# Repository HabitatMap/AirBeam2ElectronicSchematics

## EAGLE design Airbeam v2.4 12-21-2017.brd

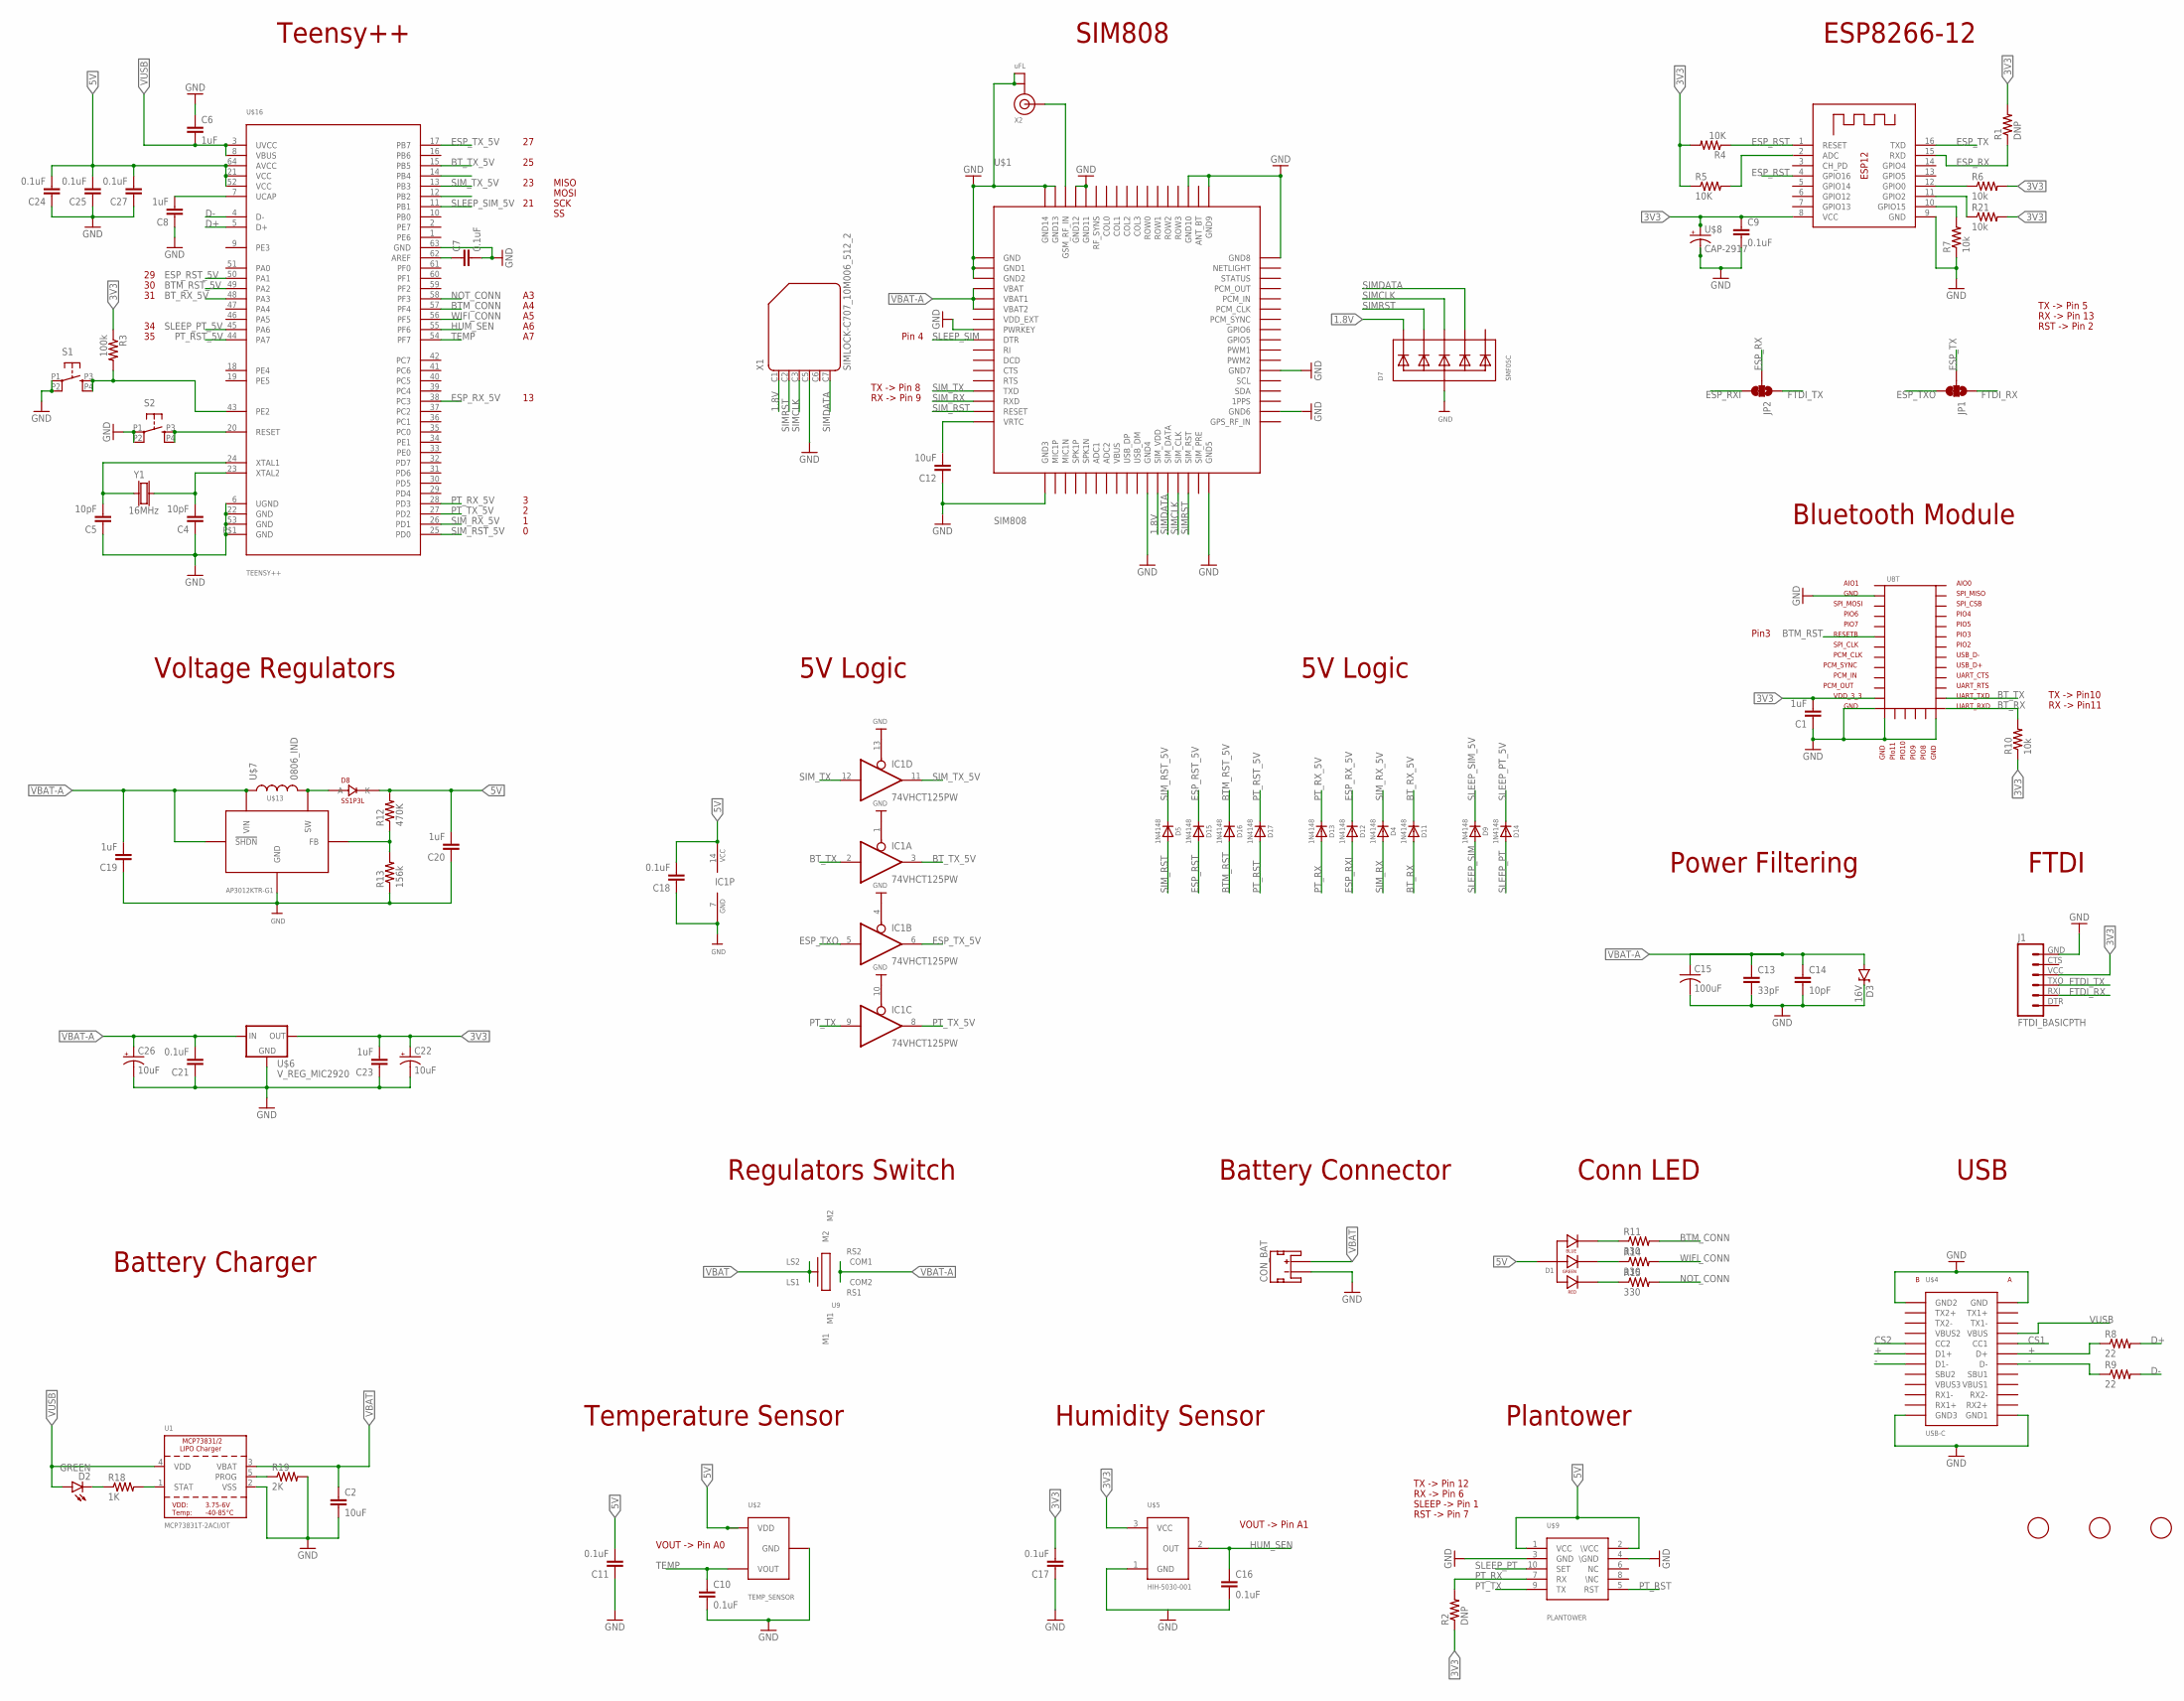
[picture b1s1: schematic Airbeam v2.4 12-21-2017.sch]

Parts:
C1, C6, C8, C19, C20, C23: 1uF; CAP0603
C2, C12: 10uF; CAP0603
C4, C5, C14: 10pF; CAP0603
C7, C9, C10, C11, C16, C17, C18, C21, C24, C25, C27: 0.1uF; CAP0603
C13: 33pF; CAP0603
C15: 100uF; C1210
C22, C26: 10uF; EIA3216
CON_BAT: CON_BAT; JST-2-SMD; PARTNO S2B-PH-SM4-TB(LF)(SN)
D1: LED1615RGBC
D2: GREEN; LED-0603
D3: 16V; SOD-123
D4, D5, D9, D11, D12, D13, D14, D15, D16, D17: 1N4148; SOD-323
D7: SMF05C; SOT363
D8: SS1P3L; DO220AAL
IC1: 74VHCT125PW; TSSOP14
J1: FTDI_BASICPTH; FTDI_BASIC
JP1, JP2: JUMPER-PAD-3-2OF3_NC_BY_TRACE_SMALL; PAD-JUMPER-3-2OF3_NC_BY_TRACE_YES_SILK_FULL_BOX
R1, R2: DNP; RES-0603
R3: 100k; RES-0603
R4, R5: 10K; RES-0603
R6, R7, R10, R21: 10k; RES-0603
R8, R9: 22; RES-0603
R11, R14, R15: 330; RES-0603
R12: 470K; RES-0603
R13: 156k; RES-0603
R18: 1K; RES-0603
R19: 2K; RES-0603
S1, S2: JAYCONSYSTEMS_TAC_SWITCHHIRO; JAYCONSYSTEMS_TS-1184
U1: MCP73831T-2ACI/OT; SOT23-5
U9: PUSHBUTTON
U$1: SIM808
U$2: TEMP_SENSOR; SOT23-3
U$3, U$12, U$14: FIDUCIAL; FIDUCIAL_1MM
U$4: USB-C
U$5: HIH-5030-001; HUM_SEN
U$6: V_REG_MIC2920; SOT223
U$7: 0806_IND; 0806
U$8: CAP-2917; EIA2917
U$9: PLANTOWER; CONN
U$13: AP3012KTR-G1; SOT23-5
U$16: TEENSY++; 64QFN
UBT: BT-NVC-MDCS42A; BT_NVC-MDCS42A
X1: SIMLOCK-C707_10M006_512_2; C707_10M006_512_2
X2: uFL; U.FL
X3: ESP-12
Y1: 16MHz; CRYSTAL-3.2X2.5

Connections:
1.8V: D7.1 (C1), U$1.29 (SIM_VDD), X1.C1 (1)
3V3: C1.2, C9.1, C17.2, C22.A (+), C23.2, J1.VCC (4), R1.2, R2.1, R3.1, R4.2, R5.1, R6.2, R10.1, R21.2, U$5.3 (VCC), U$6.3 (OUT), U$8.1 (+), UBT.P$12, X3.8 (VCC)
5V: C11.2, C18.2, C20.2, C24.2, C25.2, C27.2, D1.1 (ANODE), D8.P$1 (K), IC1.14 (VCC), R12.2, U$2.1 (VDD), U$9.1 (VCC), U$9.2 (\VCC), U$16.21 (VCC), U$16.52 (VCC), U$16.64 (AVCC)
+: R8.1, U$4.A6 (D+), U$4.B6 (D1+)
-: R9.1, U$4.A7 (D-), U$4.B7 (D1-)
BTM_CONN: R11.2, U$16.57 (PF4)
BTM_RST: D16.A, UBT.P$6
BTM_RST_5V: D16.C, U$16.49 (PA2)
BT_RX: D11.A, R10.2, UBT.P$20
BT_RX_5V: D11.C, U$16.48 (PA3)
BT_TX: IC1.2 (I), UBT.P$21
BT_TX_5V: IC1.3 (O), U$16.15 (PB5)
CS1: U$4.A5 (CC1)
CS2: U$4.B5 (CC2)
D+: R8.2, U$16.5 (D+)
D-: R9.2, U$16.4 (D-)
ESP_RST: D15.A, R4.1, X3.1 (RESET), X3.4 (GPIO16)
ESP_RST_5V: D15.C, U$16.50 (PA1)
ESP_RX: JP2.2, R1.1, X3.15 (RXD)
ESP_RXI: D12.A, JP2.3
ESP_RX_5V: D12.C, U$16.38 (PC3)
ESP_TX: JP1.2, X3.16 (TXD)
ESP_TXO: IC1.5 (I), JP1.3
ESP_TX_5V: IC1.6 (O), U$16.17 (PB7)
FTDI_RX: J1.RXI (2), JP1.1
FTDI_TX: J1.TXO (3), JP2.1
GND: C1.1, C2.2, C4.1, C5.1, C6.1, C7.2, C8.1, C9.2, C10.2, C11.1, C12.1, C13.2, C14.2, C15.2, C16.2, C17.1, C18.1, C19.1, C20.1, C21.1, C22.C (-), C23.1, C24.1, C25.1, C26.C (-), C27.1, CON_BAT.1 (-), D3.C, D7.2 (A), IC1.1 (OE), IC1.4 (OE), IC1.7 (GND), IC1.10 (OE), IC1.13 (OE), J1.GND (6), R7.1, R13.1, R19.2, S1.P1 (1), S1.P2 (2), S2.P1 (1), S2.P2 (2), U1.2 (VSS), U$1.1 (GND), U$1.2 (GND1), U$1.3 (GND2), U$1.8 (PWRKEY), U$1.18 (GND3), U$1.28 (GND4), U$1.34 (GND5), U$1.36 (GND6), U$1.40 (GND7), U$1.51 (GND8), U$1.52 (GND9), U$1.54 (GND10), U$1.64 (GND11), U$1.65 (GND12), U$1.67 (GND13), U$1.68 (GND14), U$2.3 (GND), U$4.A1 (GND), U$4.A12 (GND1), U$4.B1 (GND2), U$4.B12 (GND3), U$5.1 (GND), U$6.2 (GND), U$6.4 (GND), U$8.2 (-), U$9.3 (GND), U$9.4 (\GND), U$13.2 (GND), U$16.6 (UGND), U$16.22 (GND), U$16.53 (GND), U$16.63 (GND), U$16.P$1 (GND), UBT.P$2, UBT.P$13, UBT.P$14, UBT.P$19, X1.C5 (4), X2.1 (GND), X2.2 (GND), X3.9 (GND)
HUM_SEN: C16.1, U$5.2 (OUT), U$16.55 (PF6)
unnamed: R5.2, X3.2 (ADC)
unnamed: S2.P3 (3), S2.P4 (4), U$16.20 (RESET)
unnamed: C8.2, U$16.7 (UCAP)
unnamed: C7.1, U$16.62 (AREF)
unnamed: D2.C, R18.1
unnamed: R21.1, X3.11 (GPIO2)
unnamed: R18.2, U1.1 (STAT)
unnamed: R3.2, S1.P3 (3), S1.P4 (4), U$16.43 (PE2)
unnamed: R7.2, X3.10 (GPIO15)
unnamed: D1.4 (BLUE_CATHODE), R11.1
unnamed: U$1.66 (GSM_RF_IN), X2.3 (SIGNAL)
unnamed: C12.2, U$1.17 (VRTC)
unnamed: D1.3 (GREEN_CATHODE), R14.1
unnamed: R12.1, R13.2, U$13.3 (FB)
unnamed: R19.1, U1.5 (PROG)
unnamed: R6.1, X3.12 (GPIO0)
unnamed: D1.2 (RED_CATHODE), R15.1
unnamed: D8.P$2 (A), U$7.2, U$13.1 (SW)
unnamed: C5.2, U$16.24 (XTAL1), Y1.1
unnamed: C4.2, U$16.23 (XTAL2), Y1.3 (2)
NOT_CONN: R15.2, U$16.58 (PF3)
PT_RST: D17.A, U$9.5 (RST)
PT_RST_5V: D17.C, U$16.44 (PA7)
PT_RX: D13.A, R2.2, U$9.7 (RX)
PT_RX_5V: D13.C, U$16.28 (PD3)
PT_TX: IC1.9 (I), U$9.9 (TX)
PT_TX_5V: IC1.8 (O), U$16.27 (PD2)
SIMCLK: D7.4 (C3), U$1.31 (SIM_CLK), X1.C3 (3)
SIMDATA: D7.5 (C4), U$1.30 (SIM_DATA), X1.C7 (6)
SIMRST: D7.3 (C2), U$1.32 (SIM_RST), X1.C2 (2)
SIM_RST: D5.A, U$1.16 (RESET)
SIM_RST_5V: D5.C, U$16.25 (PD0)
SIM_RX: D4.A, U$1.15 (RXD)
SIM_RX_5V: D4.C, U$16.26 (PD1)
SIM_TX: IC1.12 (I), U$1.14 (TXD)
SIM_TX_5V: IC1.11 (O), U$16.13 (PB3)
SLEEP_PT: D14.A, U$9.10 (SET)
SLEEP_PT_5V: D14.C, U$16.45 (PA6)
SLEEP_SIM: D9.A, U$1.9 (DTR)
SLEEP_SIM_5V: D9.C, U$16.11 (PB1)
TEMP: C10.1, U$2.2 (VOUT), U$16.54 (PF7)
VBAT: C2.1, CON_BAT.2 (+), U1.3 (VBAT), U9.LS1, U9.LS2
VBAT-A: C13.1, C14.1, C15.1, C19.2, C21.2, C26.A (+), D3.A, U9.C1 (COM1), U9.C2 (COM2), U$1.4 (VBAT), U$1.5 (VBAT1), U$1.6 (VBAT2), U$6.1 (IN), U$7.1, U$13.4 (!SHDN), U$13.5 (VIN)
VUSB: C6.2, D2.A, U1.4 (VDD), U$4.A4 (VBUS), U$16.3 (UVCC), U$16.8 (VBUS)
WIFI_CONN: R14.2, U$16.56 (PF5)

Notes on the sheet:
Teensy++
SIM808
ESP8266-12
Voltage Regulators
Bluetooth Module
USB
Power Filtering
Battery Charger
Battery Connector
5V Logic
Plantower
Regulators Switch
Humidity Sensor
Temperature Sensor
RX -> Pin11
TX -> Pin10
RX -> Pin 9
TX -> Pin 8
RX -> Pin 13
TX -> Pin 5
RX -> Pin 6
TX -> Pin 12
VOUT -> Pin A0
VOUT -> Pin A1
Pin 4
RST -> Pin 2
Pin3
SLEEP -> Pin 1
RST -> Pin 7
Conn LED
FTDI
SCK
MOSI
MISO

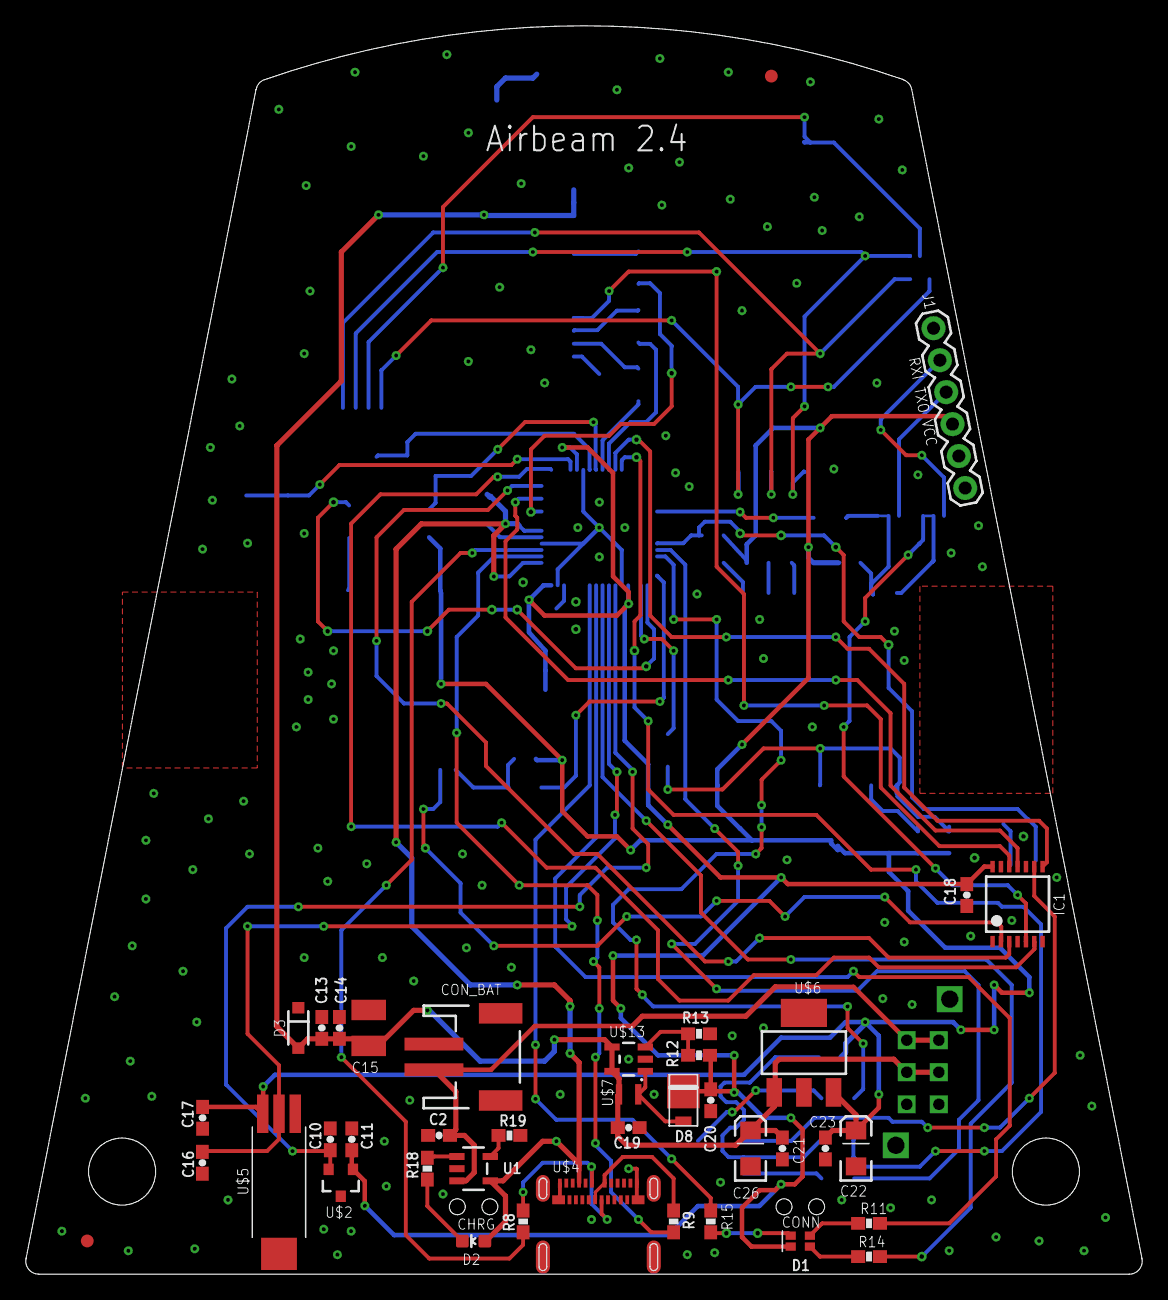
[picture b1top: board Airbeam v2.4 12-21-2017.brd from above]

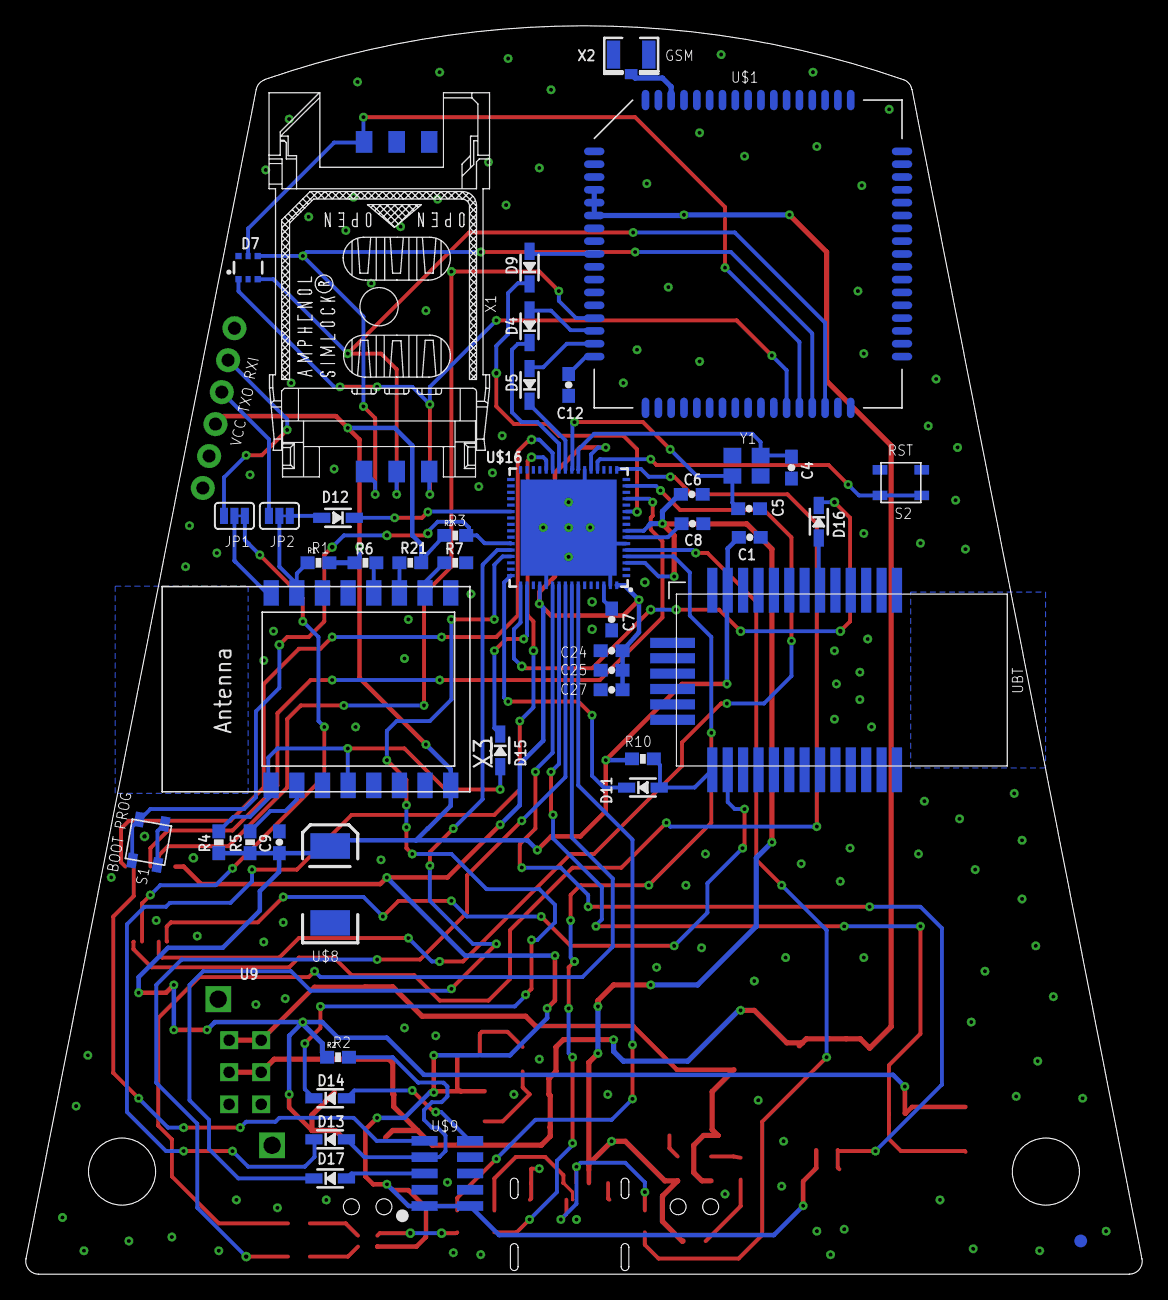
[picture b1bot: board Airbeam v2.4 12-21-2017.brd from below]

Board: 2 copper layers, 87.0 x 97.3 mm, 86 parts (46 on the bottom side), 71 nets.

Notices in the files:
parts and their libraries:
SparkFun-Connectors: Licensing: Creative Commons ShareAlike 4.0 International - https://creativecommons.org/licenses/by-sa/4.0
microbuilder: This work is placed in the public domain, and may be freely used for commercial and non-commercial work with the following conditions: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
